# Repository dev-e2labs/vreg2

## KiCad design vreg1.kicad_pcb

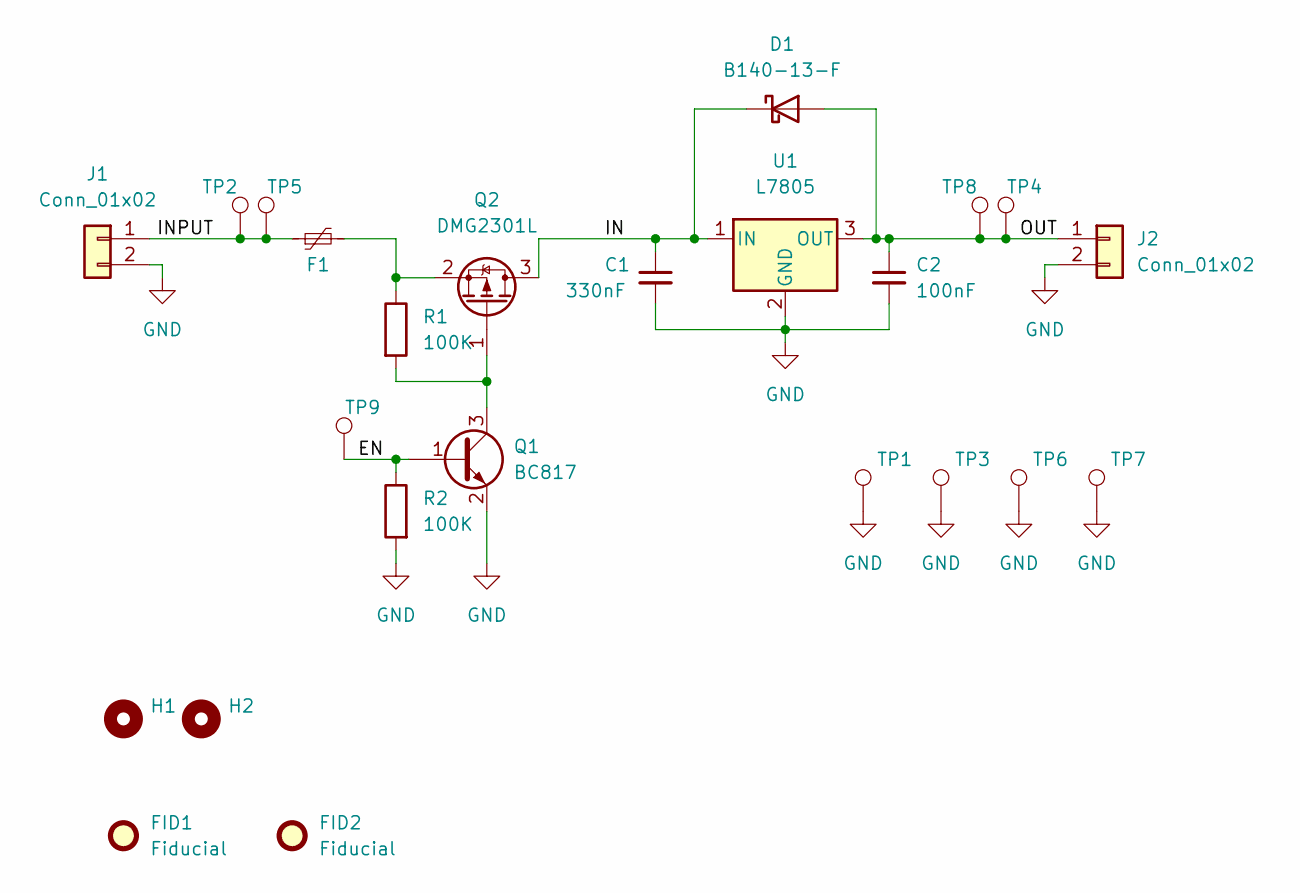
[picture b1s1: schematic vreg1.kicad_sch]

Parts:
C1: 330nF; C_1206_3216Metric; JLC_PN C274377
C2: 100nF; C_0603_1608Metric; JLC_PN C14663
D1: B140-13-F; D_SMA; JLC_PN C15759
F1: Polyfuse_Small; Fuse_1206_3216Metric; JLC_PN C841189
FID1, FID2: Fiducial; Fiducial_0.5mm_Mask1mm
H1, H2: MountingHole; MountingHole_2.1mm
J1, J2: Conn_01x02; PinHeader_1x02_P2.00mm_Vertical
Q1: BC817; SOT-23; JLC_PN C39828
Q2: DMG2301L; SOT-23; JLC_PN C150721
R1, R2: 100K; R_0603_1608Metric; JLC_PN C25803
TP1, TP3, TP6, TP7: GND; cast_edge
TP2, TP5: IN; cast_edge
TP4, TP8: OUT; cast_edge
TP9: EN; cast_edge
U1: L7805; TO-252-2; JLC_PN C55509

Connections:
/EN: Q1.1 (B), R2.1, TP9.1
/IN: C1.1, D1.1 (K), Q2.3 (D), U1.1 (IN)
/INPUT: F1.1, J1.1, TP2.1, TP5.1
/OUT: C2.1, D1.2 (A), J2.1, TP4.1, TP8.1, U1.3 (OUT)
GND: C1.2, C2.2, J1.2, J2.2, Q1.2 (E), R2.2, TP1.1, TP3.1, TP6.1, TP7.1, U1.2 (GND)
unnamed: F1.2, Q2.2 (S), R1.1
unnamed: Q1.3 (C), Q2.1 (G), R1.2

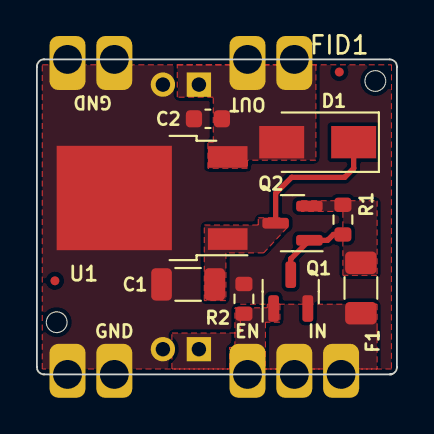
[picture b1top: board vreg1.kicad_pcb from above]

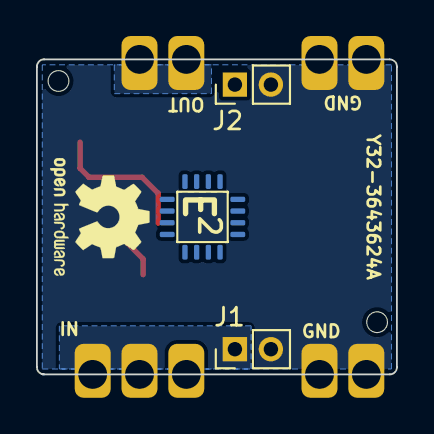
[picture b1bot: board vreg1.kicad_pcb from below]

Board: 2 copper layers, 20.0 x 17.5 mm, 25 parts (3 on the bottom side), 7 nets.

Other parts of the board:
E: QFN-16-1EP_4x4mm_P0.65mm_EP2.7x2.7mm

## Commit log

2022-02-18 Add KiCad design and fabrication files
2022-02-23 Add logotype, move GND TP to right side
    Add PDFs for schematics and BOM
2022-02-23 Add mechanical drawing of edge outline
